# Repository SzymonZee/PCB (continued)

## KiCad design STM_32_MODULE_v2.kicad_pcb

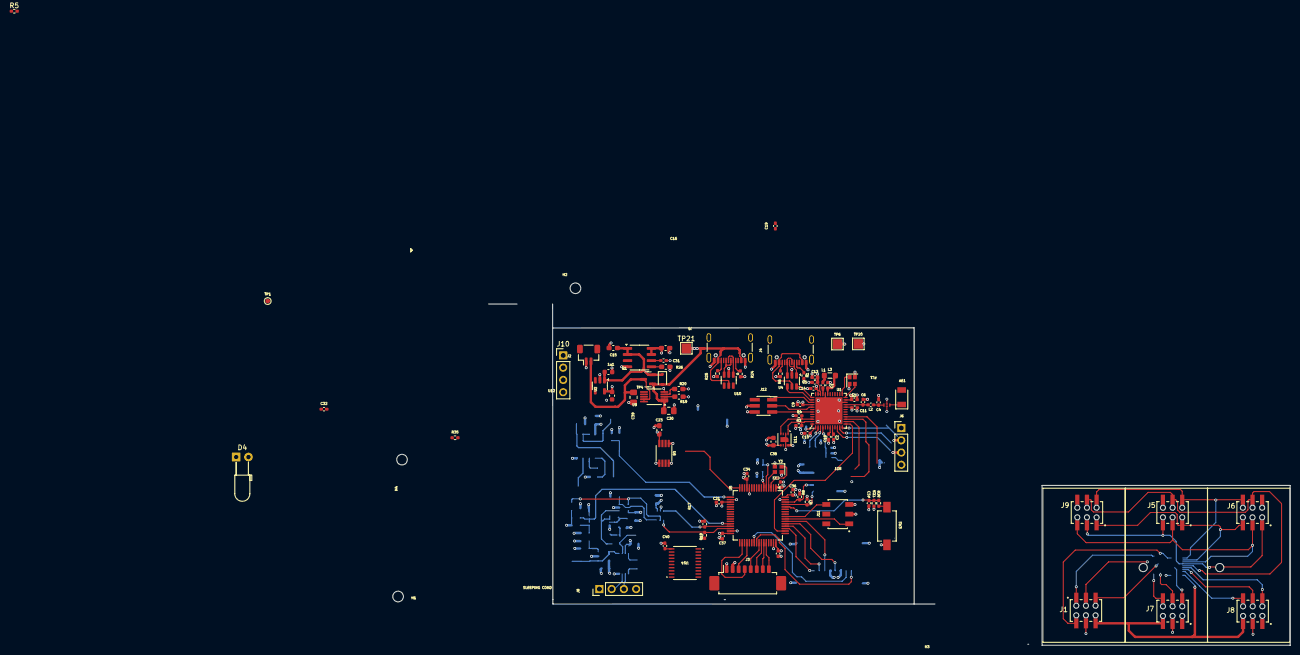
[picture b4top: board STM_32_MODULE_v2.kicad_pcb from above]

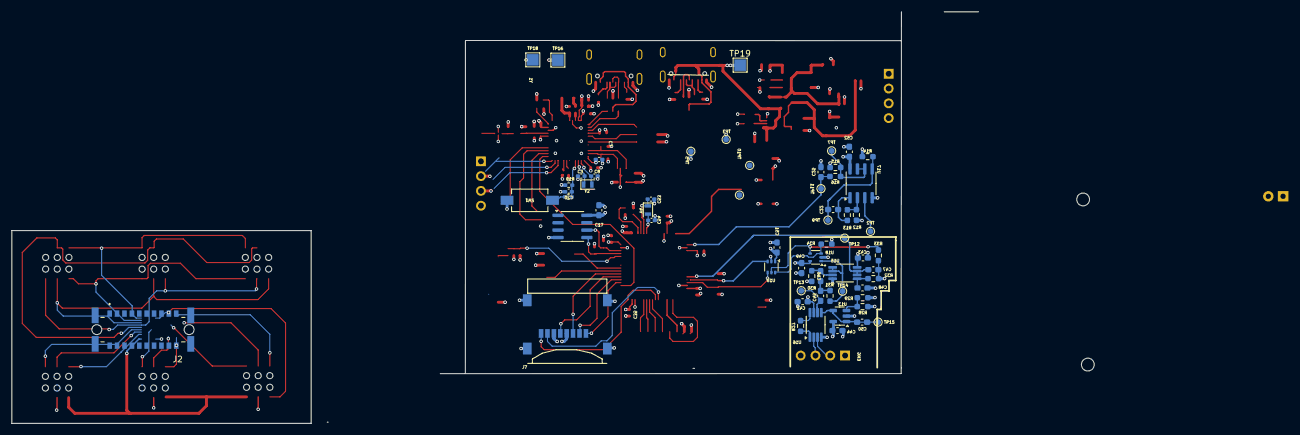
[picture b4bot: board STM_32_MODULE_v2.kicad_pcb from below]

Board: 6 copper layers, 166.0 x 70.7 mm, 154 parts (62 on the bottom side), 89 nets.

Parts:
1u1: C; C_0603_1608Metric
AE1: Antenna; ANTC3216X140N
C1, C13: 4.7uF; C_0402_1005Metric_Pad0.74x0.62mm_HandSolder
C2, C5, C7, C9, C10, C11, C12, C14, C18, C20, C21, C24, C33, C34, C35, C36, C37: 0.1uF; C_0402_1005Metric_Pad0.74x0.62mm_HandSolder
C3, C6, C53: 0.3pF; C_0402_1005Metric_Pad0.74x0.62mm_HandSolder
C4, C8, C54: 0.8pF; C_0402_1005Metric_Pad0.74x0.62mm_HandSolder
C15: 4,7uF; C_0603_1608Metric_Pad1.08x0.95mm_HandSolder
C16: 1uF; C_0603_1608Metric_Pad1.08x0.95mm_HandSolder
C17: 0.1uF; C_0603_1608Metric_Pad1.08x0.95mm_HandSolder
C19, C32, C40: 1uf; C_0402_1005Metric_Pad0.74x0.62mm_HandSolder
C22, C50: 1u; C_0603_1608Metric_Pad1.08x0.95mm_HandSolder
C23, C25: 1uf; C_0603_1608Metric_Pad1.08x0.95mm_HandSolder
C30, C39: 4.7uF; C_0805_2012Metric_Pad1.18x1.45mm_HandSolder
C31: 0,1uf; C_0402_1005Metric_Pad0.74x0.62mm_HandSolder
C38: C; C_0603_1608Metric
C41: 1u; C_0603_1608Metric
C42, C43, C49, C52: C; C_0603_1608Metric_Pad1.08x0.95mm_HandSolder
C44, C51: 100n; C_0603_1608Metric_Pad1.08x0.95mm_HandSolder
C45, C46: 470n; C_0603_1608Metric_Pad1.08x0.95mm_HandSolder
C47, C48: 2.2n; C_0603_1608Metric_Pad1.08x0.95mm_HandSolder
D1: D; D_SOD-323
D4: LED; LED_D3.0mm_Horizontal_O3.81mm_Z10.0mm
FL1: DLF162500LT-5028A1; DLF-4_1P6X0P8
H1, H2, H3, H4: MountingHole; MountingHole_2.2mm_M2
J1: M55-7022042R; HARWIN_M22-6340342
J2: Conn_01x02_Pin; JST_SH_BM02B-SRSS-TB_1x02-1MP_P1.00mm_Vertical
J2#2: Conn_01x02_Pin; HARWIN_M55-7022042R
J3: Conn_01x08_Pin; Molex_PicoBlade_53261-0871_1x08-1MP_P1.25mm_Horizontal
J4, J5#2: USB_C_Receptacle_USB2.0_16P; USB_C_Receptacle_GCT_USB4105-xx-A_16P_TopMnt_Horizontal
J5: USB_C_Receptacle_USB2.0_16P; HARWIN_M22-6340342
J6, J8, J10: Conn_01x04_Pin; PinHeader_1x04_P2.54mm_Vertical
J6#2, J8#2: Conn_01x04_Pin; HARWIN_M22-6340342
J7: molex_sd_card; HARWIN_M22-6340342
J7#2: molex_sd_card; MOLEX_47219-2001
J9: Conn_01x05_Pin; HARWIN_M22-6340342
J11: Conn_01x06_Pin; HARWIN_M22-5320305
J12: Conn_01x06_Pin; PinSocket_2x03_P1.27mm_Vertical_SMD
L1: 10nH; C_0402_1005Metric_Pad0.74x0.62mm_HandSolder
L2: 2.7nH; C_0402_1005Metric_Pad0.74x0.62mm_HandSolder
L3: 10uH; L_0805_2012Metric_Pad1.05x1.20mm_HandSolder
Q1: IRLML5203; SOT-23
R1, R24: 5.1K; R_0402_1005Metric_Pad0.72x0.64mm_HandSolder
R3, R4, R5, R7, R8, R17, R18: 4.7k; R_0402_1005Metric_Pad0.72x0.64mm_HandSolder
R6, R10, R25, R37: 5.1k; R_0402_1005Metric_Pad0.72x0.64mm_HandSolder
R11, R36: 200; R_0402_1005Metric_Pad0.72x0.64mm_HandSolder
R12, R15, R34: 1k; R_0603_1608Metric_Pad0.98x0.95mm_HandSolder
R13: 10k; R_0603_1608Metric_Pad0.98x0.95mm_HandSolder
R14: 330k; R_0603_1608Metric_Pad0.98x0.95mm_HandSolder
R16: 16k; R_0603_1608Metric_Pad0.98x0.95mm_HandSolder
R19, R20: 4,7k; C_0603_1608Metric_Pad1.08x0.95mm_HandSolder
R26: 100k; C_0603_1608Metric_Pad1.08x0.95mm_HandSolder
R27, R28, R29: R; R_0603_1608Metric_Pad0.98x0.95mm_HandSolder
R30, R31, R32: 68k; R_0603_1608Metric_Pad0.98x0.95mm_HandSolder
R33: 2,7k; R_0603_1608Metric_Pad0.98x0.95mm_HandSolder
R35: 100k; R_0402_1005Metric_Pad0.72x0.64mm_HandSolder
SW1, SW3: RS-282G05A3-SM RT; RS-282G05A3-SM RT_CNK
TP1, TP2, TP3, TP4, TP5, TP7, TP9, TP10, TP11, TP12, TP13, TP14, TP15: TestPoint; TestPoint_Pad_D1.0mm
TP6, TP16, TP18, TP19, TP20, TP21: TestPoint; TestPoint_Pad_2.0x2.0mm
U1: STM32WB55CCU6; QFN-48-1EP_7x7mm_P0.5mm_EP5.6x5.6mm
U2: MCP1802T-3302I/OT; SOT-23-5
U3: ATECC608A-SSHDA; SOIC-8_3.9x4.9mm_P1.27mm
U4, U10: USBLC6-2SC6; SOT-23-6
U5: STM32L476RGTx; LQFP-64_10x10mm_P0.5mm
U6: MCP4541-104E/MS; MSOP8_MC_MCH
U9: MCP73833-xxx-UN; MSOP-10_3x3mm_P0.5mm
U11: SHT31-DIS; Sensirion_DFN-8-1EP_2.5x2.5mm_P0.5mm_EP1.1x1.7mm
U12: MCP1727-3302xSN; SOIC-8_3.9x4.9mm_P1.27mm
U13: MCP6001; SOT-23-5
U14: AT42QT2120-XUR; TSSOP20_MC_MCH-L
U15: MCP6002; mcp60002
U16: INA333; VSSOP-8_3x3mm_P0.65mm
U17: OPA2376xxD; SOIC-8_3.9x4.9mm_P1.27mm
U18: TLV9001IDCK; SOT-353_SC-70-5
U19: MCP4018; SOT-363_SC-70-6
Y1, Y3: 32Mhz; Crystal_SMD_2016-4Pin_2.0x1.6mm
Y2: 32kHz768; Crystal_SMD_2012-2Pin_2.0x1.2mm
Y4: 32kHz; Crystal_SMD_2012-2Pin_2.0x1.2mm

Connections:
+3.3V: C2.1, C5.1, C7.1, C9.1, C10.1, C11.1, C12.1, C13.1, C14.1, C16.1, C17.1, C19.1, C21.1, C23.2, C32.2, C33.1, C34.1, C35.1, C36.1, C37.1, C38.1, C40.1, C51.1, J3.1, J6.3, J6#2.3, J7.4 (VDD), J7#2.4 (VDD), J10.1, J11.3, J12.6, R3.1, R4.1, R5.2, R7.2, R8.1, R17.2, R18.1, R19.1, R20.1, R26.1, SW1.2, SW3.2, TP5.1, TP6.1, TP16.1, U1.1 (VBAT), U1.8 (VDDA), U1.20 (VDD), U1.23 (VDDRF), U1.34 (VDDSMPS), U1.35 (VDD), U1.40 (VDDUSB), U1.48 (VDD), U3.8 (VCC), U5.1 (VBAT), U5.13 (VDDA), U5.19 (VDD), U5.32 (VDD), U5.48 (VDDUSB), U5.64 (VDD), U6.8 (VDD), U11.5 (VDD), U12.7 (Sense), U12.8 (Vout), U14.11 (VDD), U19.1 (VDD)
+3.3_AVDD: C41.1, C42.1, C43.1, C44.1, C49.1, C52.1, J9.2, R28.1, U2.5 (VOUT), U13.5 (V+), U15.8 (V+), U16.7 (V+), U17.8 (V+), U18.5 (V+)
BL: J3.8, U5.44 (PA11)
C02_IN: J6.4, J6#2.4
CLK: J3.4, U5.34 (PB13)
CS: J3.5, U5.41 (PA8)
DIN: J3.3, U5.36 (PB15)
DS: J3.6, U5.42 (PA9)
EMG +: J8.2, J8#2.2, U16.3 (+)
EMG RG: J8.4, J8#2.4, R27.2, U16.8 (Rg)
EMG-: J8.3, J8#2.3, U16.2 (-)
EMG_OUT: C47.1, TP12.1, U5.28 (PB2), U15.6 (-), U15.7
GND: 1u1.2, C1.1, C2.2, C3.1, C4.1, C5.2, C6.1, C7.2, C8.1, C9.2, C10.2, C11.2, C12.2, C13.2, C14.2, C15.2, C16.2, C17.2, C18.2, C19.2, C20.2, C21.2, C23.1, C24.2, C25.1, C30.2, C31.2, C32.1, C33.2, C34.2, C35.2, C36.2, C37.2, C38.2, C39.2, C40.2, C41.2, C42.2, C43.2, C44.2, C48.2, C49.2, C51.2, C52.2, C53.1, C54.1, FL1.2 (GND), FL1.4 (GND), J2.1, J3.2, J4.A1 (GND), J4.A12 (GND), J4.B1 (GND), J4.B12 (GND), J4.S1 (SHIELD), J5#2.A1 (GND), J5#2.A12 (GND), J5#2.B1 (GND), J5#2.B12 (GND), J5#2.S1 (SHIELD), J6.2, J6#2.2, J7.6 (VSS), J7#2.6 (VSS), J7#2.G1 (GND@1), J7#2.G2 (GND@2), J7#2.G3 (GND@3), J7#2.G4 (GND@4), J9.3, J10.2, J11.5, J12.4, R1.2, R6.2, R10.1, R12.1, R14.2, R15.1, R24.2, R25.2, R29.2, R30.2, R34.1, R37.1, TP1.1, TP3.1, TP18.1, TP20.1, U1.22 (VSSRF), U1.32 (VSSSMPS), U1.49 (VSS), U2.2 (GND), U3.4 (GND), U4.2 (GND), U5.12 (VSSA), U5.18 (VSS), U5.31 (VSS), U5.47 (VSS), U5.63 (VSS), U6.1 (HVC/A0), U6.4 (VSS), U6.5 (P0A), U9.5 (V_{SS}), U10.2 (GND), U11.2 (ADDR), U11.7 (R), U11.8 (VSS), U11.9 (VSS), U12.4 (GND), U13.2 (V-), U14.10 (VSS), U15.4 (V-), U16.4 (V-), U17.4 (V-), U18.2 (V-), U19.2 (VSS), Y1.2, Y1.4, Y3.2, Y3.4
JTCK-SWCLK: J12.3, U1.41 (PA14)
JTMS-SWDIO: J12.1, U1.39 (PA13)
LM35: J6.1, J6#2.1
unnamed: AE1.1 (A), FL1.3 (OUT)
unnamed: C22.2, R13.2, U17.1
unnamed: C45.1, C46.2, R31.2
unnamed: C45.2, TP13.1, U16.6
unnamed: C47.2, R32.1, R33.2
unnamed: C4.2, FL1.1 (IN), L2.1
unnamed: C39.1, J2.2, Q1.3 (D), U9.9 (V_{BAT}), U9.10 (V_{BAT})
unnamed: J4.A5 (CC1), R1.1
unnamed: J4.B5 (CC2), R6.1
unnamed: J4.A6 (D+), J4.B6 (D+), U4.3 (I/O2)
unnamed: J4.A7 (D-), J4.B7 (D-), U4.1 (I/O1)
unnamed: J5#2.A5 (CC1), R24.1
unnamed: J5#2.B5 (CC2), R25.1
unnamed: J5#2.A6 (D+), J5#2.B6 (D+), U10.3 (I/O2)
unnamed: J5#2.A7 (D-), J5#2.B7 (D-), U10.1 (I/O1)
unnamed: L1.1, L3.2
unnamed: R11.1, SW1.1
unnamed: R27.1, U16.1 (Rg)
unnamed: R36.1, SW3.1
unnamed: U1.25 (OSC_IN), Y1.1
unnamed: U1.24 (OSC_OUT), Y1.3
unnamed: C8.2, U1.2 (PC14), Y2.2
unnamed: C3.2, U1.3 (PC15), Y2.1
unnamed: C20.1, R10.2, R11.2, U1.4 (PH3)
unnamed: C6.2, L2.2, U1.21 (RF1)
unnamed: C1.2, L3.1, U1.31 (VFBSMPS)
unnamed: L1.2, U1.33 (VLXSMPS)
unnamed: C24.1, R36.2, R37.2, U5.60 (BOOT0)
unnamed: U5.3 (PC14), Y3.1
unnamed: U5.4 (PC15), Y3.3
unnamed: C53.2, U5.5 (PH0), Y4.1
unnamed: C54.2, U5.6 (PH1), Y4.2
unnamed: C31.1, U12.6 (Cdelay)
unnamed: R26.2, U12.5 (PWRGD)
unnamed: R28.2, R29.1, U13.3 (+)
unnamed: C50.1, C50.2, TP15.1, U13.1, U13.4 (-), U16.5 (Ref)
unnamed: C46.1, R30.1, U15.3 (+)
unnamed: R31.1, TP14.1, U15.1, U15.2 (-), U18.1 (+)
unnamed: C48.1, R32.2, U15.5 (+)
unnamed: R12.2, R13.1, U17.2 (-)
unnamed: C22.1, R14.1, TP9.1, U17.5 (+)
unnamed: R34.2, U18.3 (-), U19.6 (A)
unnamed: R33.1, U18.4, U19.5 (W)
PA11: U1.37 (PA11), U4.6 (I/O1), U10.6 (I/O1)
PA12: U1.38 (PA12), U4.4 (I/O2), U10.4 (I/O2)
POB: R15.2, R16.1, TP7.1, TP10.1, U6.6 (P0W), U6.7 (P0B), U17.6 (-), U17.7
PPG_IN: J9.1, TP2.1, U17.3 (+)
PPG_OUT: C25.2, R16.2, TP11.1, U5.17 (PA3)
RST: J3.7, U5.43 (PA10)
SCL: R4.2, U1.46 (PB6), U11.4 (SCL)
SCL2_L4: R17.1, U5.29 (PB10), U19.3 (SCL)
SCL_L4: R7.1, U3.5 (SDA), U5.61 (PB8), U6.2 (SCL)
SDA: R3.2, U1.47 (PB7), U11.1 (SDA)
SDA2_L4: R18.2, U5.30 (PB11), U19.4 (SDA)
SDA_L4: R8.2, TP4.1, U3.6 (SCL), U5.62 (PB9), U6.3 (SDA)
SDMMC1_CK_L4: J7.5 (CLK), J7#2.5 (CLK), U5.53 (PC12)
SDMMC1_CMD_L4: J7.3 (CMD), J7#2.3 (CMD), U5.54 (PD2)
SDMMC1_D0_L4: J7#2.7 (DAT0), U5.39 (PC8)
SDMMC1_D1_L4: J7#2.8 (DAT1), U5.40 (PC9)
SDMMC1_D2_L4: J7.1 (DAT2), J7#2.1 (DAT2), U5.51 (PC10)
SDMMC1_D3_L4: J7.2 (CD/DAT3), J7#2.2 (CD/DAT3), U5.52 (PC11)
SPI_1_MOSI: R5.1, U1.16 (PA7)
SPI_1_NSS: U1.13 (PA4), U5.50 (PA15)
STAT1: R19.2, U9.3 (STAT1)
STAT2: R20.2, U9.4 (STAT2)
SWCLK_L47: J11.4, U5.49 (PA14)
SWDIO_L47: J11.2, U5.46 (PA13)
SWD_NRST: C18.1, U1.7 (NRST)
SWD_NRST_L47: J11.6, U5.56 (PB4)
SWD_SWO: J12.5, U1.43 (PB3)
SWD_TRACE_L47: J11.1, U5.55 (PB3)
VBUS: C30.1, D1.2 (A), J4.A4 (VBUS), J4.A9 (VBUS), J4.B4 (VBUS), J4.B9 (VBUS), J5#2.A4 (VBUS), J5#2.A9 (VBUS), J5#2.B4 (VBUS), J5#2.B9 (VBUS), Q1.1 (G), TP19.1, TP21.1, U4.5 (VBUS), U9.1 (V_{DD}), U9.2 (V_{DD}), U10.5 (VBUS)
Vsup: 1u1.1, C15.1, D1.1 (K), Q1.2 (S), U2.1 (VIN), U12.1 (Vin), U12.2 (Vin)
